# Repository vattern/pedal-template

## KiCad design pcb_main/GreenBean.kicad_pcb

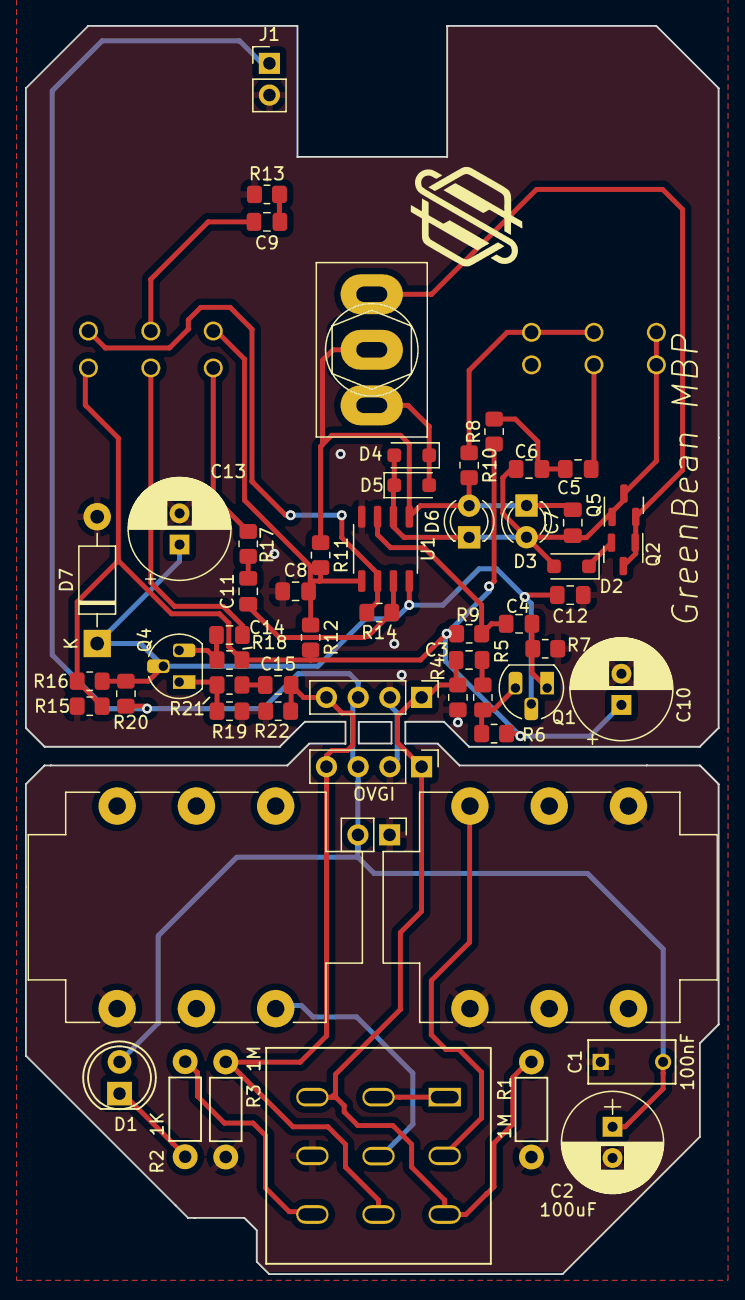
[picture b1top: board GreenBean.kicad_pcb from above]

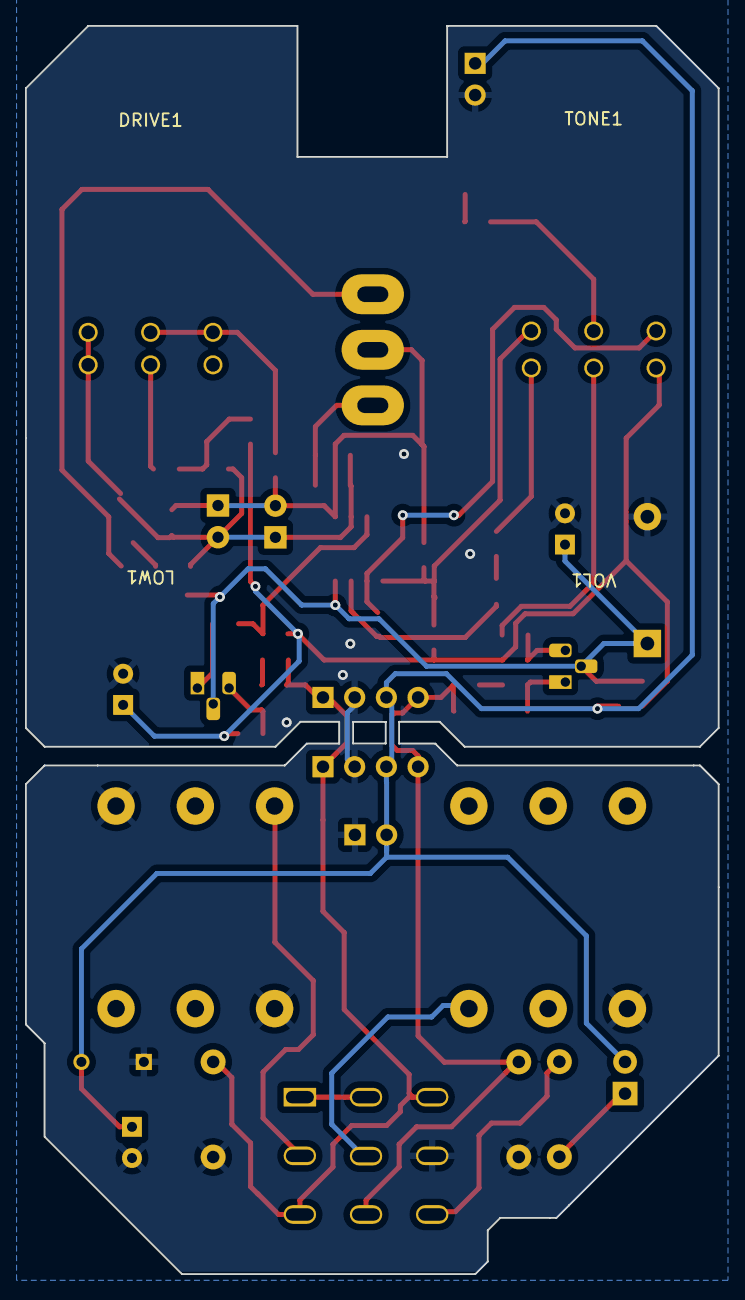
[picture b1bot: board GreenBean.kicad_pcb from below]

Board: 2 copper layers, 55.5 x 100.0 mm, 62 parts (4 on the bottom side), 34 nets.

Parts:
C1: 100nF; C_Rect_L7_W3.5_P5
C2, C13: 100uF; CP_Radial_D8.0mm_P2.50mm
C3: 20n; C_0805_2012Metric_Pad1.18x1.45mm_HandSolder
C4, C11, C15: 1u; C_0805_2012Metric_Pad1.18x1.45mm_HandSolder
C5: 150n; C_0805_2012Metric_Pad1.18x1.45mm_HandSolder
C6: 47n; C_0805_2012Metric_Pad1.18x1.45mm_HandSolder
C7: 51p; C_0805_2012Metric_Pad1.18x1.45mm_HandSolder
C8, C9, C12: 220n; C_0805_2012Metric_Pad1.18x1.45mm_HandSolder
C10: 10uF; CP_Radial_D8.0mm_P2.50mm
C14: 100n; C_0805_2012Metric_Pad1.18x1.45mm_HandSolder
D1: LED; LED-5MM
D2: BAT41; D_SOD-123F
D3, D6: LED; LED_D3.0mm
D4, D5: 1N914; D_SOD-123F
D7: 1N4001; D_DO-41_SOD81_P10.16mm_Horizontal
DRIVE1: 500KA; Potentiometer_ALPHA_RV16106N
J1, J4: V+ GND; PinHeader_1x02_P2.54mm_Vertical
J2, J3: NMJ6HCD2; Jack_6.35mm_Neutrik_NMJ6HCD2_Horizontal
JOVGI1, JOVGI2: OVGI; Pin_Header_Straight_1x04_Pitch2.54mm
LOW1: 20KB; Potentiometer_ALPHA_RV16106N
N1: Housing; 1590B
Q1, Q4: 2SC1815; TO-92L_HandSolder
Q2, Q5: 2N7002; SOT-23
R1, R3: 1M; Resistor_Horizontal_RM7mm
R2: 1K; Resistor_Horizontal_RM7mm
R4: 1M; R_0805_2012Metric_Pad1.20x1.40mm_HandSolder
R5, R11, R14, R17: 1k; R_0805_2012Metric_Pad1.20x1.40mm_HandSolder
R6, R18: 510k; R_0805_2012Metric_Pad1.20x1.40mm_HandSolder
R7, R9, R12, R15, R16, R19, R22: 10k; R_0805_2012Metric_Pad1.20x1.40mm_HandSolder
R8: 4k7; R_0805_2012Metric_Pad1.20x1.40mm_HandSolder
R10: 51k; R_0805_2012Metric_Pad1.20x1.40mm_HandSolder
R13: 220R; R_0805_2012Metric_Pad1.20x1.40mm_HandSolder
R20: 47R; R_0805_2012Metric_Pad1.20x1.40mm_HandSolder
R21: 100R; R_0805_2012Metric_Pad1.20x1.40mm_HandSolder
SW1: SW_3PDT; 3PDT-Footswitch
SW2: SW_SPDT; SW_Toggle_Blue_wSlots
TONE1: 20KB; Potentiometer_ALPHA_RV16106N
U1: RC4558; SO-8_3.9x4.9mm_P1.27mm
VOL1: 100KB; Potentiometer_ALPHA_RV16106N

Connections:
+9V: C1.2, C2.1, D1.2 (A), J1.1, J4.2, JOVGI1.3, JOVGI2.3, R20.2
A: C6.2, C7.1, D2.2 (A), D3.2 (A), D4.2 (A), D5.1 (K), D6.1 (K), DRIVE1.1, LOW1.3, Q5.1 (G), Q5.3 (D), U1.2 (-)
B: C7.2, D3.1 (K), D6.2 (A), R10.2, R11.1, SW2.2, U1.1
GND: C1.1, C2.2, C8.1, C10.2, C12.1, C13.2, D7.2 (A), J1.2, J2.S, J2.TN, J3.S, J4.1, JOVGI1.2, JOVGI2.2, R1.2, R3.2, R4.1, R7.1, R13.1, R15.1, R19.1, R22.1, SW1.6 (B), U1.4 (V-)
I: C3.1, JOVGI1.1, JOVGI2.1, R1.1, R4.2, SW1.3 (A), SW1.7 (C)
unnamed: C3.2, R5.2
unnamed: C5.1, C6.1, R8.2
unnamed: C5.2, LOW1.2
unnamed: C9.1, R13.2
unnamed: C9.2, TONE1.2
unnamed: C11.1, R14.2, U1.7
unnamed: C11.2, R17.1
unnamed: C14.1, VOL1.2
unnamed: C15.1, R21.2
unnamed: D1.1 (K), R2.1
unnamed: D2.1 (K), Q2.2 (S)
unnamed: D4.1 (K), D5.2 (A), SW2.1
unnamed: DRIVE1.2, DRIVE1.3, R10.1
unnamed: Q1.3 (B), R5.1, R6.1
unnamed: C4.1, Q1.1 (E), R7.2
unnamed: Q2.1 (G), Q2.3 (D), Q5.2 (S), SW2.3
unnamed: C14.2, Q4.3 (B), R18.1
unnamed: Q4.1 (E), R19.2, R21.1
unnamed: R17.2, VOL1.3
unnamed: SW1.1 (A), SW1.2 (A)
unnamed: J2.T, SW1.4 (B)
unnamed: J3.T, SW1.5 (B)
unnamed: R2.2, SW1.9 (C)
unnamed: C4.2, R9.1, U1.3 (+)
unnamed: C8.2, R11.2, R12.1, TONE1.1, U1.5 (+)
unnamed: R14.1, TONE1.3, U1.6 (-)
O: C15.2, JOVGI1.4, JOVGI2.4, R3.1, R22.2, SW1.8 (C)
VB: C10.1, R6.2, R8.1, R9.2, R12.2, R15.2, R16.1, R18.2, VOL1.1
VC: C12.2, C13.1, D7.1 (K), Q1.2 (C), Q4.2 (C), R16.2, R20.1, U1.8 (V+)

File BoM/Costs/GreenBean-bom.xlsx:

|  | KiBot Bill of Materials
 |  | Schematic: | GreenBean | Component Groups: | 39
 |  | Variant: | default | Component Count: | 62 (36 SMD/ 25 THT)
 |  | Revision: |  | Fitted Components: | 62 (36 SMD/ 25 THT)
 |  | Date: | 2023-08-08_15-24-33 | Number of PCBs: | 1
 |  | KiCad Version: | 7.0.5.1-1-g8f565ef7f0-dirty-deb11 | Total Components: | 62
Row | Description | Part | References | Value | Footprint | Quantity Per PCB | Status | Datasheet | Sim.Device | Sim.Pins
1 | Unpolarized capacitor, small symbol | C_Small | C7 | 51p | C_0805_2012Metric_Pad1.18x1.45mm_HandSolder | 1 |  | ~
2 | Unpolarized capacitor, small symbol | C_Small | C3 | 20n | C_0805_2012Metric_Pad1.18x1.45mm_HandSolder | 1 |  | ~
3 | Unpolarized capacitor, small symbol | C_Small | C6 | 47n | C_0805_2012Metric_Pad1.18x1.45mm_HandSolder | 1 |  | ~
4 |  | C-device | C1 | 100nF | C_Rect_L7_W3.5_P5 | 1
5 | Unpolarized capacitor, small symbol | C_Small | C14 | 100n | C_0805_2012Metric_Pad1.18x1.45mm_HandSolder | 1 |  | ~
6 | Unpolarized capacitor, small symbol | C_Small | C5 | 150n | C_0805_2012Metric_Pad1.18x1.45mm_HandSolder | 1 |  | ~
7 | Unpolarized capacitor, small symbol | C_Small | C8 C9 C12 | 220n | C_0805_2012Metric_Pad1.18x1.45mm_HandSolder | 3 |  | ~
8 | Unpolarized capacitor, small symbol | C_Small | C4 C11 C15 | 1u | C_0805_2012Metric_Pad1.18x1.45mm_HandSolder | 3 |  | ~
9 | Polarized capacitor | C_Polarized | C10 | 10uF | CP_Radial_D8.0mm_P2.50mm | 1 |  | ~
10 | Polarized capacitor | C_Polarized | C13 | 100uF | CP_Radial_D8.0mm_P2.50mm | 1 |  | ~
11 |  | CP-device | C2 | 100uF | CP_Radial_D8.0mm_P2.50mm | 1
12 | 50V 1A General Purpose Rectifier Diode, DO-41 | 1N4001 | D7 | 1N4001 | D_DO-41_SOD81_P10.16mm_Horizontal | 1 |  | http://www.vishay.com/docs/88503/1n4001.pdf | D | 1=K 2=A
13 | 100V 0.3A Small Signal Fast Switching Diode, DO-35 | 1N914 | D4 D5 | 1N914 | D_SOD-123F | 2 |  | http://www.vishay.com/docs/85622/1n914.pdf | D | 1=K 2=A
14 | 100V 0.1A Small Signal Schottky Diode, DO-35 | BAT41 | D2 | BAT41 | D_SOD-123F | 1 |  | http://www.vishay.com/docs/85659/bat41.pdf
15 |  | LED-device | D1 | LED | LED-5MM | 1 |  | ~
16 | Light emitting diode | LED | D3 D6 | LED | LED_D3.0mm | 2 |  | ~
17 | Potentiometer | R_Potentiometer | DRIVE1 | 500KA | Potentiometer_Alpha_RD901F-40-00D_Single_Vertical | 1 |  | ~
18 | M Series, 6.35mm (1/4in) stereo jack, switched, with chrome ferrule and straigh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 | NMJ6HCD2 | J2 J3 | NMJ6HCD2 | Jack_6.35mm_Neutrik_NMJ6HCD2_Horizontal | 2 |  | https://www.neutrik.com/en/product/nmj6hcd2
19 |  | CONN_01X02-conn | J1 J4 | V+ GND | PinHeader_1x02_P2.54mm_Vertical | 2
20 |  | CONN_01X04-conn | JOVGI1 JOVGI2 | OVGI | Pin_Header_Straight_1x04_Pitch2.54mm | 2
21 | Potentiometer | R_Potentiometer | LOW1 TONE1 | 20KB | Potentiometer_Alpha_RD901F-40-00D_Single_Vertical | 2 |  | ~
22 | Housing | Housing | N1 | Housing | 1590B | 1 |  | ~
23 | 0.115A Id, 60V Vds, N-Channel MOSFET, SOT-23 | 2N7002 | Q2 Q5 | 2N7002 | SOT-23 | 2 |  | https://www.onsemi.com/pub/Collateral/NDS7002A-D.PDF
24 | NPN transistor, emitter/collector/base | Q_NPN_ECB | Q1 Q4 | 2SC1815 | TO-92L_HandSolder | 2 |  | ~
25 | Resistor | R | R20 | 47R | R_0805_2012Metric_Pad1.20x1.40mm_HandSolder | 1 |  | ~
26 | Resistor | R | R21 | 100R | R_0805_2012Metric_Pad1.20x1.40mm_HandSolder | 1 |  | ~
27 | Resistor | R | R13 | 220R | R_0805_2012Metric_Pad1.20x1.40mm_HandSolder | 1 |  | ~
28 | Resistor | R | R5 R11 R14 R17 | 1k | R_0805_2012Metric_Pad1.20x1.40mm_HandSolder | 4 |  | ~
29 |  | R-device | R2 | 1K | Resistor_Horizontal_RM7mm | 1
30 | Resistor | R | R8 | 4k7 | R_0805_2012Metric_Pad1.20x1.40mm_HandSolder | 1 |  | ~
31 | Resistor | R | R7 R9 R12 R15 R16 R19 R22 | 10k | R_0805_2012Metric_Pad1.20x1.40mm_HandSolder | 7 |  | ~
32 | Resistor | R | R10 | 51k | R_0805_2012Metric_Pad1.20x1.40mm_HandSolder | 1 |  | ~
33 | Resistor | R | R6 R18 | 510k | R_0805_2012Metric_Pad1.20x1.40mm_HandSolder | 2 |  | ~
34 |  | R-device | R1 R3 | 1M | Resistor_Horizontal_RM7mm | 2
35 | Resistor | R | R4 | 1M | R_0805_2012Metric_Pad1.20x1.40mm_HandSolder | 1 |  | ~
36 |  | SW_3PDT-switches | SW1 | SW_3PDT | 3PDT-Footswitch | 1
37 | Switch, single pole double throw, center OFF position | SW_SPDT_MSM | SW2 | SW_SPDT | SW_Toggle_Blue_wSlots | 1 |  | ~
38 | Dual General Purpose, Operational Amplifier, DIP-8/SOIC-8/SSOP-8 | RC4558 | U1 | RC4558 | SO-8_3.9x4.9mm_P1.27mm | 1 |  | http://www.ti.com/lit/ds/symlink/rc4558.pdf
39 | Potentiometer | R_Potentiometer | VOL1 | 100KB | Potentiometer_Alpha_RD901F-40-00D_Single_Vertical | 1 |  | ~

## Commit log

2023-08-08 Test new template
2023-08-08 update workflow repo
2023-08-08 Deploying to main from @ vattern/pedal-template@4406eb39d102c5341f7da6999116fb60e9c35660 🚀
2023-08-08 Test
2023-08-09 Deploying to main from @ vattern/pedal-template@ebb9dbceea1217fffab616e9c20a580bcc9802a0 🚀
2023-08-09 tests
2023-08-09 Deploying to main from @ vattern/pedal-template@6494f273b31d6ca1a14054aa98b53be1452f4365 🚀
2023-08-09 Deploying to main from @ vattern/pedal-template@29b9f412c031b5ce4274d51221edd427fa28aa7c 🚀
2023-08-09 Set output folder
2023-08-09 put back
2023-08-09 Deploying to main from @ vattern/pedal-template@88131a4e5dc37b6fac887efbb74884288330e327 🚀
2023-08-09 add 3d models
2023-08-09 Deploying to main from @ vattern/pedal-template@95a7c3263cc8d1ce57496527cf7e31c464036a77 🚀
2023-08-09 poke blender render
2023-08-09 Deploying to main from @ vattern/pedal-template@39eb587efe4dbdf7f32520e4e2929a7a364ab68f 🚀
2023-08-09 Deploying to main from @ vattern/pedal-template@7bc3ad588d28e10196cf4ffc620b7079a2e9390d 🚀
2023-08-09 make settings chanmges
2023-08-09 Deploying to main from @ vattern/pedal-template@07db35f22845307e0bf5fdbfc57d32de9645fe26 🚀
2023-08-09 Update more model folder
2023-08-09 Deploying to main from @ vattern/pedal-template@afa50abe6f633519a0061d1f09a3973784c4c45e 🚀
2023-08-09 Fix paths
2023-08-09 Deploying to main from @ vattern/pedal-template@202e39b27288d0cf91c69769d3e5067e7a17dc95 🚀
2023-08-09 attempt 3d downloads
2023-08-09 Deploying to main from @ vattern/pedal-template@d8883e9725c11ddd56e1ec7247ead895ba42e0a3 🚀
2023-08-09 Update render
2023-08-09 Deploying to main from @ vattern/pedal-template@0bc909db4afd3cf84973ccaa2064ef27bcc84b67 🚀
2023-08-09 attempt 3d models
2023-08-09 Deploying to main from @ vattern/pedal-template@b74c4c60c840b42ead6629f9bd73ecbae76068e5 🚀
2023-08-10 Add stencil
2023-08-10 Deploying to main from @ vattern/pedal-template@0e252daf3a16a5140395bbf4c647d4053751ecd4 🚀
